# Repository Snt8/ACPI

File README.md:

# 🚦 ACPI: Asistente de Cruce Peatonal para Invidentes v3.5 👨‍🦯➡️

## Descripción General
**ACPI** es un sistema **IoT de asistencia a la movilidad** que da **autonomía y seguridad** a personas con discapacidad visual al cruzar calles con semáforo.

Un **semáforo** (baliza fija en la esquina) transmite su orientación y la luz peatonal por ESP-NOW. Un **brazalete** lee la orientación de la persona con su propia brújula, la compara con la del cruce y le indica con vibraciones hacia dónde girar y cuándo la luz está en verde o en rojo. Por Bluetooth Low Energy (BLE) el brazalete envía su telemetría a una **app móvil** accesible (iOS y Android), que avisa por voz y registra los cruces en la **API de ACPI**. Las cifras anónimas se publican en **[ACPI Web](https://snt8.github.io/acpi-website/)**.

Esta es la versión 3.5: PCB propia para el brazalete, firmware reescrito para Arduino IDE / ESP-IDF y app en React Native. La versión 2, que ganó la **medalla de oro en Infomatrix Sudamérica 2025**, está en el [repositorio original](https://github.com/Dilaansg/ACPI).

---

## Contenido
- `firmware/brazalete/` -> Firmware del brazalete (ESP32-C3 Super Mini): sketch de Arduino IDE que también compila con ESP-IDF, con pruebas en la PC (`test/`) y sketches de prueba del hardware (`pruebas/`). Los patrones de vibración están en `patrones.md`. Ver su README.
- `firmware/semaforo/` -> Firmware del semáforo (ESP32 DevKit V1), con la misma estructura. Ver su README.
- `app-movil/` -> App móvil para iOS y Android (React Native + Expo), pensada para usarse con VoiceOver y TalkBack. Ver su README.
- `docs/` -> Protocolos y diseño:
  - `ble-protocol.md`: contrato BLE entre el brazalete y la app.
  - `servidor-api.md`: contrato HTTPS entre la app y la API.
  - `guia-app-invidentes.md`: guía de diseño accesible de la app.
  - `figuras/`: figura de arquitectura, que también usa el sitio web.
- `electronics/` -> PCB del brazalete en EasyEDA: `acpiv3.5-design` (la placa v3.5, la que está en uso) y `acpiv3-new-design`. Cada carpeta trae esquemático, BOM y Gerbers.
- `3D-models/` -> Carcasa del brazalete. Los STL se generan con `generar_case.py`; para cambiar la carcasa se cambian sus parámetros, no las mallas.
- `assets/` -> Logos de ACPI (el vigente es `ACPI-V3.5-Logo-updated.pdf`).

El sitio web y la API están en otro repositorio: **[Snt8/acpi-website](https://github.com/Snt8/acpi-website)**.

---

## Explicación
### Arquitectura y Flujo de Procesamiento

```text
[Semáforo ESP32] ─ESP-NOW─► [Brazalete ESP32-C3] ─BLE─► [App móvil] ─HTTPS─► [ACPI API] ──► [ACPI Web]
 QMC6308                     QMC5883L + MPU6500         iOS / Android        FastAPI +       GitHub Pages
 2 LEDs simulan la luz       Brújula a 5 Hz             Voz y lector          Supabase en
 25 s por luz                2 motores de vibración     de pantalla, GPS      Render
 Paquete a 2 Hz              Standby sin semáforo       Semáforos guardados   (acpi-website/api)
```

1. **Semáforo (infraestructura)**: un ESP32 DevKit V1 con un magnetómetro QMC6308 mide su orientación, ya calibrada y promediada. Simula con dos LEDs un ciclo de 25 s por luz. Cada 500 ms transmite por ESP-NOW (broadcast) un paquete de 10 bytes con su rumbo, la luz y el tiempo restante; el paquete lleva la firma `"ACPI"` y un CRC-8.
2. **Brazalete (wearable)**: un ESP32-C3 Super Mini en la PCB v3.5, con un GY-271 (QMC5883L) y un MPU6500. Calcula a 5 Hz su rumbo con calibración *hard-iron* y compensación de inclinación. La persona queda de frente al cruce cuando `|Δθ − 180°| < 5°` en dos lecturas seguidas.
   - Con dos micromotores indica el lado hacia el que hay que girar y luego avisa la luz peatonal: verde con dos pulsos largos, rojo con uno. Cada evento vibra una sola vez.
   - Tras 30 s sin paquetes del semáforo pasa a **standby**: apaga sensores, motores y BLE, y escucha 1.2 s cada 5 s.
3. **App móvil (iOS y Android)**: se conecta al brazalete por BLE. El brazalete sólo enciende el BLE cerca de un semáforo, así que la app lo busca y se reconecta sola.
   - Describe el estado del cruce por voz o con el lector de pantalla, sin ordenar nunca cruzar.
   - Guarda los semáforos del usuario en el teléfono.
   - Mide cada cruce con el GPS (espera, duración, paquetes perdidos, señal) y lo envía a la API. Si no hay red, lo guarda en una cola local.
4. **ACPI API y ACPI Web** ([acpi-website](https://github.com/Snt8/acpi-website)): la API (FastAPI + Supabase, que se despliega en Render con `render.yaml`) recibe los eventos `cruce` y `semaforo` según el contrato de `docs/servidor-api.md`. El sitio en GitHub Pages presenta el proyecto y publica el panel de telemetría con datos anónimos.

---

## Dependencias
- **Hardware**:
  - Brazalete: ESP32-C3 Super Mini sobre la PCB v3.5, MPU6500 (I2C 0x68), GY-271 con QMC5883L (I2C 0x0D), 2 micromotores de vibración tipo moneda y batería LiPo con conector JST-PH.
  - Semáforo: ESP32 DevKit V1, magnetómetro QMC6308 (I2C 0x2C) y 2 LEDs.
- **Software**:
  - [Arduino IDE](https://www.arduino.cc/en/software) con el paquete *esp32 by Espressif Systems* 3.x (probado con 3.3.9), o ESP-IDF 5.5.
  - g++ o clang++ para las pruebas del brazalete en la PC (en Windows, el de WSL).
  - Node 20 o superior, y una Mac con Xcode (iOS) o Android Studio (Android) para compilar la app. La app usa módulos nativos (Bluetooth, MapLibre), así que necesita un *development build*; no funciona en Expo Go.
  - Python 3 con `numpy`, `trimesh` y `manifold3d` para regenerar la carcasa.

---

## Ejemplo de Uso

Los dos firmwares son sketches de Arduino IDE (también compilan con ESP-IDF). Hay que abrir
`firmware/brazalete/brazalete.ino` o `firmware/semaforo/semaforo.ino` en Arduino IDE y
cargarlos con la placa que indica el README de cada uno.

Desde la terminal con `arduino-cli`:
```bash
# Brazalete (ESP32-C3 Super Mini, Serial por el USB nativo)
arduino-cli compile --fqbn esp32:esp32:esp32c3:CDCOnBoot=cdc firmware/brazalete

# Semáforo (ESP32 DevKit V1)
arduino-cli compile --fqbn esp32:esp32:esp32 firmware/semaforo
```

Las pruebas de la lógica del brazalete corren en la PC, sin placa (ver
`firmware/brazalete/test/README.md`):
```bash
sh firmware/brazalete/test/ejecutar_pruebas.sh
```

La app se compila e instala en el teléfono con un *development build*. Para iOS, desde una
Mac, con `npx expo run:ios --device` (los pasos están en `app-movil/README.md`):
```bash
cd app-movil
npm install
npx expo run:android
```

Para probar la app con el brazalete real, el semáforo tiene que estar encendido cerca: el
brazalete no enciende el Bluetooth hasta recibir su primer paquete.

---

## Autores
- **Edy S. Avila** ([@Snt8](https://github.com/Snt8))
- **Dilan Osorio** ([@Dilaansg](https://github.com/Dilaansg))
- **Andrea Cárdenas** ([@AndreaCarod](https://github.com/AndreaCarod))
- **Nicolás Rodríguez** ([@NicolasRodriguez08](https://github.com/NicolasRodriguez08))

Dilan, Andrea y Nicolás formaron el equipo de ACPI v2, en el [repositorio original](https://github.com/Dilaansg/ACPI).

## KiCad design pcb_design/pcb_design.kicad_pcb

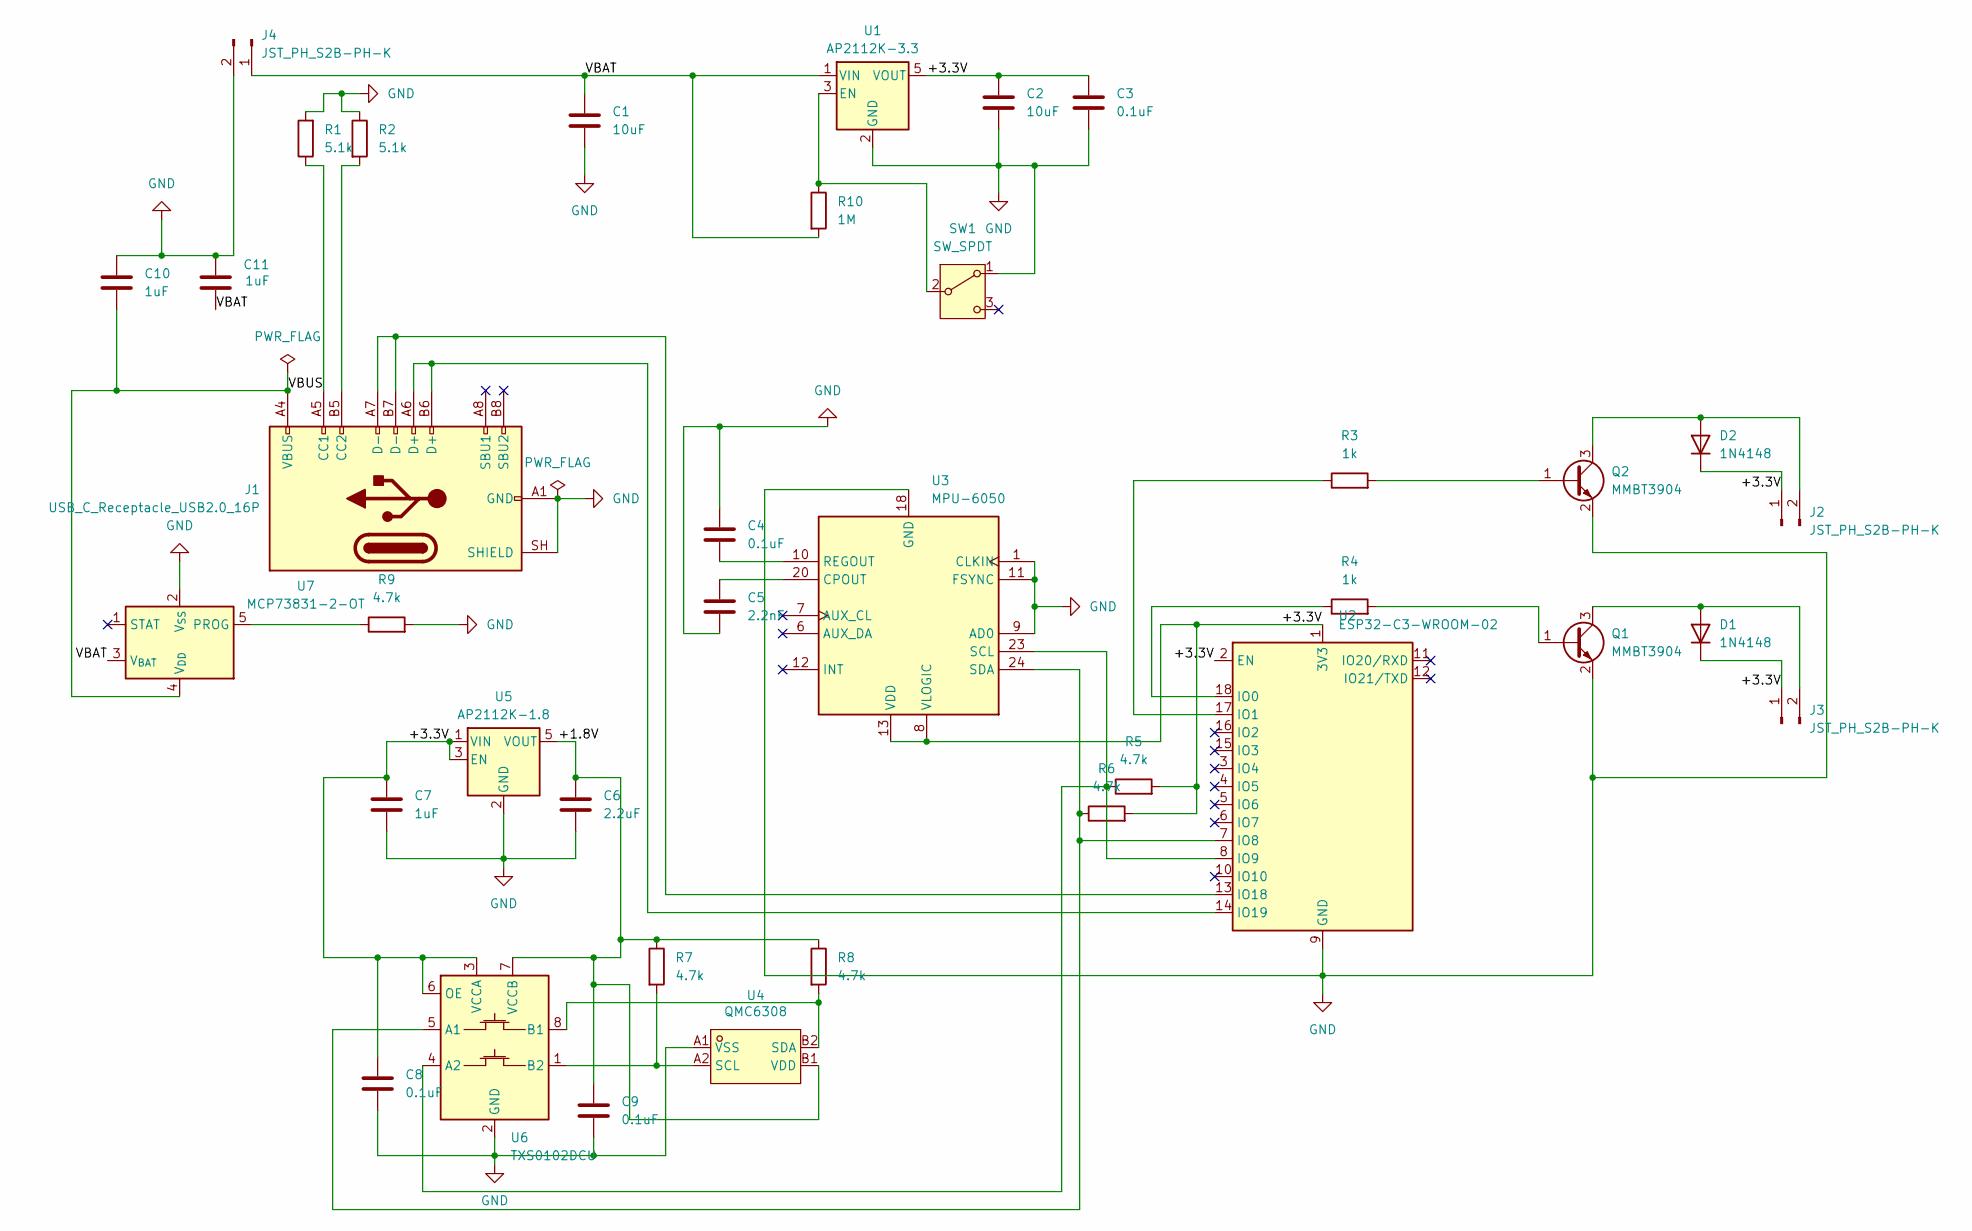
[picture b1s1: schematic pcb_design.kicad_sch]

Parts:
C1, C2: 10uF; C_0805_2012Metric
C3, C4, C8, C9: 0.1uF; C_0603_1608Metric
C5: 2.2nF; C_0603_1608Metric
C6: 2.2uF; C_0805_2012Metric
C7: 1uF; C_0603_1608Metric
C10, C11: 1uF; C_0805_2012Metric
D1, D2: 1N4148; D_DO-35_SOD27_P7.62mm_Horizontal
J1: USB_C_Receptacle_USB2.0_16P; USB_C_Receptacle_HRO_TYPE-C-31-M-12
J2, J3, J4: JST_PH_S2B-PH-K; JST_PH_S2B-PH-K_1x02_P2.00mm_Horizontal
Q1, Q2: MMBT3904; SOT-23
R1, R2: 5.1k; R_0603_1608Metric
R3, R4: 1k; R_0603_1608Metric
R5, R6, R7, R8, R9: 4.7k; R_0603_1608Metric
R10: 1M; R_0603_1608Metric
SW1: SW_SPDT; SW_SPDT_Shouhan_MSK12C02
U1: AP2112K-3.3; SOT-23-5
U2: ESP32-C3-WROOM-02
U3: MPU-6050; InvenSense_QFN-24_4x4mm_P0.5mm
U4: QMC6308; WLCSP-4_L0.8-W0.8-R2-C2-P0.40-BL; MPN QMC6308; LCSC Part C462705
U5: AP2112K-1.8; SOT-23-5
U6: TXS0102DCU; VSSOP-8_2.3x2mm_P0.5mm
U7: MCP73831-2-OT; SOT-23-5

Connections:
/+1.8V: C6.1, C9.1, R7.1, R8.1, U4.B1 (VDD), U5.5 (VOUT), U6.7 (VCCB)
/+3.3V: C2.1, C3.1, C7.1, C8.1, D1.1 (K), D2.1 (K), J2.1, J3.1, R5.2, R6.2, U1.5 (VOUT), U2.1 (3V3), U2.2 (EN), U3.8 (VLOGIC), U3.13 (VDD), U5.1 (VIN), U5.3 (EN), U6.3 (VCCA), U6.6 (OE)
/VBAT: C1.1, C11.2, J4.1, R10.2, U1.1 (VIN), U7.3 (V_{BAT})
/VBUS: C10.2, J1.A4 (VBUS), J1.A9 (VBUS), J1.B4 (VBUS), J1.B9 (VBUS), U7.4 (V_{DD})
GND: C1.2, C2.2, C3.2, C4.2, C5.1, C6.2, C7.2, C8.2, C9.2, C10.1, C11.1, J1.A1 (GND), J1.A12 (GND), J1.B1 (GND), J1.B12 (GND), J1.SH (SHIELD), J4.2, Q1.2 (E), Q2.2 (E), R1.2, R2.1, R9.2, SW1.1 (A), U1.2 (GND), U2.9 (GND), U2.19 (GND), U3.1 (CLKIN), U3.9 (AD0), U3.11 (FSYNC), U3.18 (GND), U4.A1 (VSS), U5.2 (GND), U6.2 (GND), U7.2 (V_{SS})
unnamed: D1.2 (A), J3.2, Q1.3 (C)
unnamed: D2.2 (A), J2.2, Q2.3 (C)
unnamed: J1.A5 (CC1), R1.1
unnamed: J1.B5 (CC2), R2.2
unnamed: Q1.1 (B), R4.2
unnamed: Q2.1 (B), R3.2
unnamed: R10.1, SW1.2 (B), U1.3 (EN)
unnamed: R4.1, U2.18 (IO0)
unnamed: R3.1, U2.17 (IO1)
unnamed: R6.1, U2.7 (IO8), U3.24 (SDA), U6.5 (A1)
unnamed: R5.1, U2.8 (IO9), U3.23 (SCL), U6.4 (A2)
unnamed: J1.A7 (D-), J1.B7 (D-), U2.13 (IO18)
unnamed: J1.A6 (D+), J1.B6 (D+), U2.14 (IO19)
unnamed: C5.2, U3.20 (CPOUT)
unnamed: C4.1, U3.10 (REGOUT)
unnamed: R7.2, U4.A2 (SCL), U6.1 (B2)
unnamed: R8.2, U4.B2 (SDA), U6.8 (B1)
unnamed: R9.1, U7.5 (PROG)

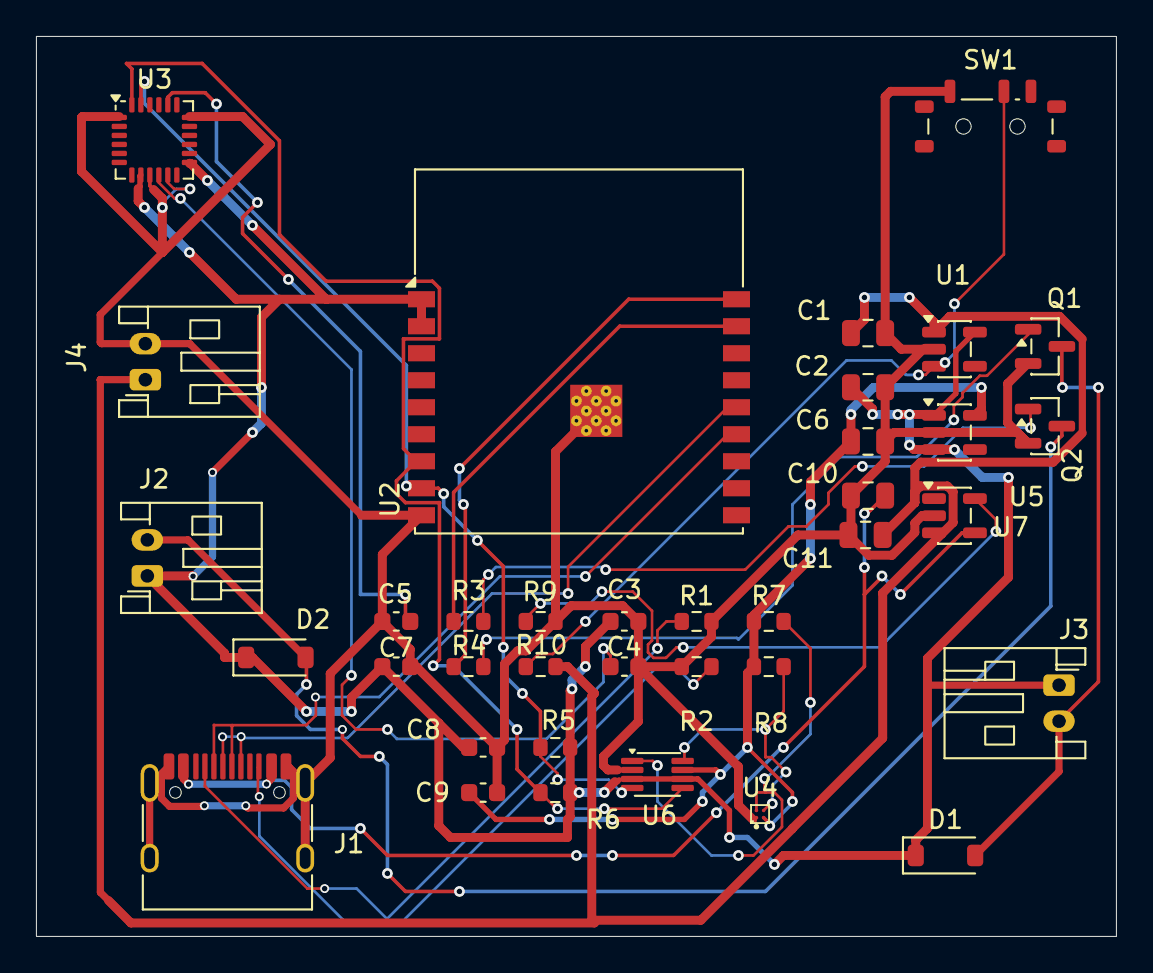
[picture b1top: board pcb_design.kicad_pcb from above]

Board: 2 copper layers, 60.0 x 50.0 mm, 37 parts (0 on the bottom side), 23 nets.

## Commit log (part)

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2026-05-05 Remove sensitive data from google-services.json
    Removed sensitive project information from google-services.json.
2026-05-09 chore: implementar el .gitignore
2026-05-09 refactor: implementar directorio dedicado al firmware
2026-05-09 refactor: implementar directorios docs y tools para la documentacion y el dashboard
2026-05-09 chore: traer codigo inicial de firmware
2026-05-11 chore: implementar nueva estructura para el firmware de la pulsera
2026-05-11 chore: eliminar archivos
2026-05-11 feat: implementar estructura del archivo platformio.ini
2026-05-12 feat: implementar configuracion de PlatformIO
2026-05-13 chore: finalizar configuracion de PlatformIO
2026-05-13 feat: comenzar la implementacion del firmware para la pulsera
2026-05-16 chore: renombrar los archivos de funcionalidades de la pulsera
2026-05-17 feat: implementar estructura de datos de la comunicacion
2026-05-17 chore: mover la estructura de los datos de directorio
2026-05-18 feat: implementar la estructura para la comunicacion de la pulsera mediante ESP-NOW
2026-05-18 chore: eliminar archivos innecesarios
2026-05-18 chore: actualizar la estructura del archivo de configuracion de PlatformIO
2026-05-18 feat: implementar la logica de la comunicacion de la pulsera
2026-05-19 feat: implementar la cabecera con la descripcion del controlador para el acelerometro
2026-05-19 feat: implementar la logica del controlador del acelerometro
2026-05-19 feat: implementar la cabecera con la descripcion del controlador del magnetometro
2026-05-19 feat: implementar la logica del controlador del magnetometro
2026-05-20 feat:implementar la estructura de cabecera de control de los motores
2026-05-20 feat: implementar logica del control de los motores
2026-05-20 feat; implementar la cabecera del controlador de la brujula
2026-05-20 feat: implementar loigca del controlador de la brujula
2026-05-21 feat: implementar funcion para controlar los momentos de vibracion de los motores
2026-05-21 feat: implementar logica de la funcion para controlar los momentos de vibracion de los motores
2026-05-21 feat: implementar la cabecera de la funcion para determinar la direccion del semaforo
2026-05-21 feat: implementar la logica de la funcion para determinar la direccion del semaforo
2026-05-21 feat: implementar la funcion para verificar la direccion en el metodo de verificacion del semaforo en la brujula
2026-05-21 refactor: exponer atributo del heading actual de la brujula
2026-05-21 fix: inicializar los atributos de los sensores en los archivos .cpp
2026-05-21 feat: implementar la cabecera de la vibracion para indicar un error en la inicializacion de la pulsera
2026-05-21 feat: implementar la logica del setup y loop para el micro-controlador
2026-05-23 feat: implementar parametros y constantes de configuracion
2026-05-23 refactor: incluir constantes y parametros de archivos de configuracion
2026-05-23 feat: implementar la logica para indicar un error con patrones de vibracion
2026-05-23 feat: implementar un parametro de configuracion de tiempo
2026-05-26 chore: estructura para sender
2026-06-04 feat: implementar elementos de debuging y mejora del sistema
2026-06-06 feat: implementar la estructura para el firmware del semaforo
2026-06-06 docs: documentar modulos de la pulsera
2026-06-06 feat: implementar la estructura para la comunicacion de datos desde el semaforo
2026-06-06 feat: initialize project agents, embedded architecture rules, and build automation with Justfile
2026-06-06 feat: implement ACPI core architecture with BLE/ESP-NOW communication, state machine logic, and Grafana telemetry reporting
2026-06-17 feat: implementar la logica final para el correcto funcionamiento del componente de firmware y documentar
2026-06-17 feat: implementar la actualizacion a la aplicacion y documentar
2026-06-17 docs: documentacion del proyecto
